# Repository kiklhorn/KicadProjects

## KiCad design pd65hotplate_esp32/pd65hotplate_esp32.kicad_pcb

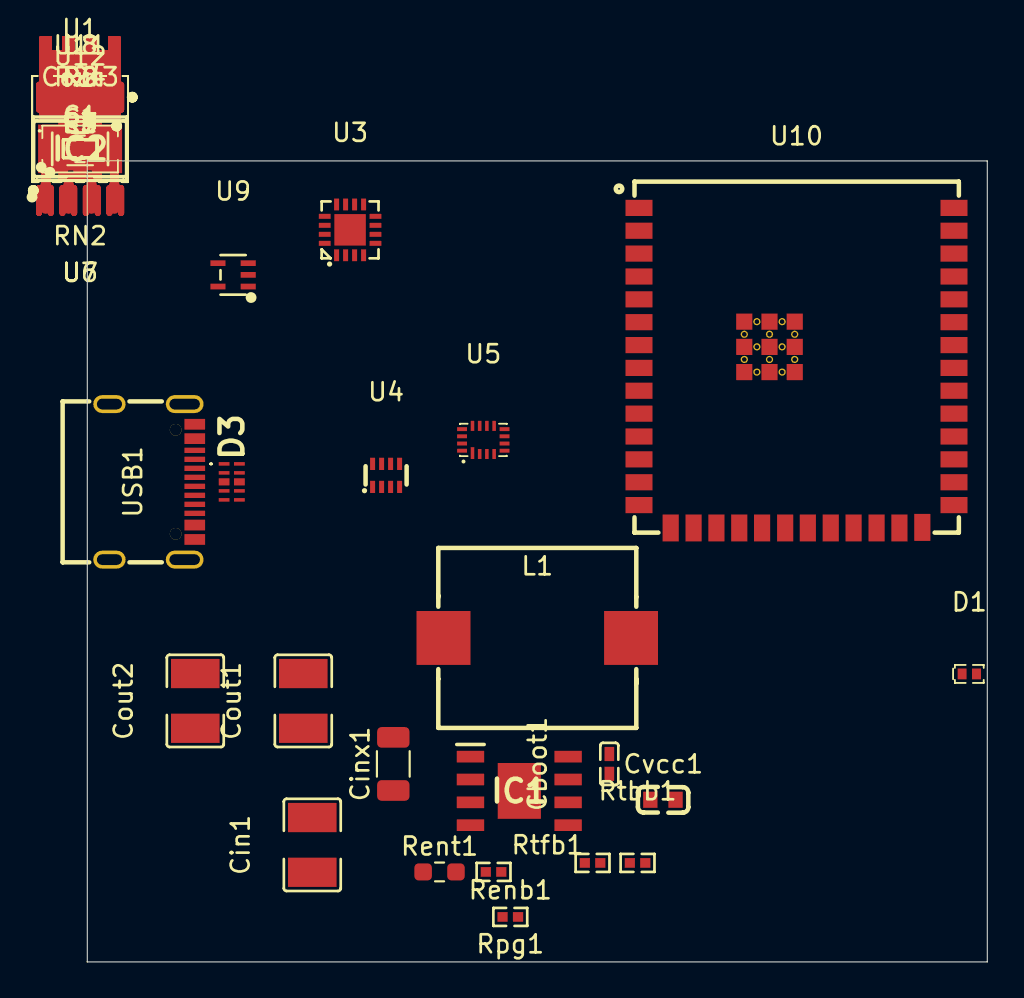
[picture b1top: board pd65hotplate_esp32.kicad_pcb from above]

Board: 2 copper layers, 50.0 x 44.5 mm, 42 parts (0 on the bottom side), 40 nets, no tracks yet.

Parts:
C1: 220n/100V; C_1206_3216Metric
C3: 105K50V; C_0603_1608Metric_Pad1.08x0.95mm_HandSolder
C4: 22p; C_0805_2012Metric_Pad1.18x1.45mm_HandSolder
Cboot1: GRM155R71A104KA01D; C0402
Cin1: GCM32DC72A475KE02L; C1210
Cinx1: 220n/100V; C_1206_3216Metric
Cout1, Cout2, Cout3: GRM32ER61C476KE15L; C1210
Cvcc1: EMK107B7105KA-T; C0603
D1: PESD24VS1UL-N; DFN1006-2L-RD
D3: PESD4USB5U-TTSX; PESD4USB5UTTSX
IC1: LMR36510FADDAR; SOIC127P600X170-9N
IC2: BQ25173QWDRCRQ1
L1: SDR1105-220ML; IND-SMD_L11.0-W10.0-2
R1: 920k; R_0603_1608Metric_Pad0.98x0.95mm_HandSolder
R2: 50k; R0402
R3: 10R; R_0603_1608Metric_Pad0.98x0.95mm_HandSolder
R4, R7, R8: 900k; R_0603_1608Metric_Pad0.98x0.95mm_HandSolder
R5: R_0603_1608Metric_Pad0.98x0.95mm_HandSolder
R6: R0402
R24: 10k; R0402
RN2: 100k; RES-ARRAY-SMD_16P-L3.8-W1.6-P0.50-BL
Renb1: CRCW0402100KFKED; R0402
Rent1: CRCW0402100KFKED; R_0603_1608Metric_Pad0.98x0.95mm_HandSolder
Rpg1: CRCW0402100KFKED; R0402
Rtbb1: CRCW040243K2FKED; R0402
Rtfb1: CRCW0402100KFKED; R0402
U1: RT9068GSP; ESOP-8_L4.9-W3.9-P1.27-LS6.0-BL-EP2.3
U3: HUSB238A; QFN-16_L3.0-W3.0-P0.50-BL-EP1.7
U4: LM66200DRLR; SOT-583-8_L2.1-W1.2-P0.50-LS1.6-BL
U5: FSA2567UMX; UMLP-16_L2.6-W1.8-P0.40-BL
U6, U7: 74HC4051PW,118; TSSOP-16_L5.0-W4.4-P0.65-LS6.4-BL
U8, U11: AGM60P90A; TDSON-8_L5.9-W5.2-P1.27-BL
U9: 74AHC1G14SE-7; SOT-353_L2.1-W1.3-P0.65-LS2.3-BR
U10: ESP32-S3-WROOM-1U-N16R8; WIRELM-SMD_ESP32-S3-WROOM-1U
U12: SY6280AAAC; TSOT-23-5_L2.9-W1.6-P0.95-LS2.8-BL
USB1: TYPEC-304A-ACP16G; USB-C-SMD_XUNPU_TYPEC-304A-ACP16W

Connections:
3V3: R7.1, R8.1, RN2.10 (R7.2), RN2.11 (R6.2), RN2.12 (R5.2), RN2.13 (R4.2), RN2.14 (R3.2), RN2.15 (R2.2), RN2.16 (R1.2), U3.5 (VDD), U4.2 (VOUT), U4.7 (VOUT), U5.14 (VCC), U6.16 (VCC), U7.16 (VCC), U9.5 (VCC), U10.11 (3V3)
3V3bck: U4.6 (VIN2), U12.1 (OUT)
3V3smps: C4.1, Cout2.2, Cout3.2, L1.1, Rpg1.2, Rtfb1.1, U4.3 (VIN1), U12.4 (EN), U12.5 (IN)
CC1: D3.1 (CH1), U3.3 (CC1), USB1.A5 (CC1)
CC2: D3.5 (CH4), U3.4 (CC2), USB1.B5 (CC2)
DN: D3.2 (CH2), U3.2 (D-), USB1.A7 (DN1), USB1.B7 (DN2)
DP: D3.4 (CH3), U3.1 (D+), USB1.A6 (DP1), USB1.B6 (DP2)
GND: C1.2, C3.2, Cin1.2, Cinx1.2, Cout1.1, Cout2.1, Cout3.1, Cvcc1.1, D3.3 (GND_1), D3.8 (GND_2), IC1.1 (PGND), IC1.9 (THERMAL), R2.2, R24.2, Renb1.2, Rtbb1.2, U1.5 (SHDN), U1.6 (GND), U1.7 (GND), U1.9 (EP), U3.17 (GND), U4.1 (GND), U4.4 (~ON), U4.5 (GND), U5.6 (GND), U6.4 (Y7), U6.6 (~E), U6.7 (VEE), U6.8 (GND), U7.4 (Y7), U7.7 (VEE), U7.8 (GND), U9.3 (GND), U10.12 (GND), U12.2 (GND), USB1.25 (EH), USB1.26 (EH), USB1.27 (EH), USB1.28 (EH), USB1.A1 (GND), USB1.A12 (GND), USB1.B1 (GND), USB1.B12 (GND)
unnamed: R5.2, R6.1
unnamed: Cboot1.2, IC1.7 (BOOT)
unnamed: IC1.3 (EN), Renb1.1, Rent1.2
unnamed: C4.2, IC1.5 (FB), Rtbb1.1, Rtfb1.2
unnamed: IC1.4 (PG), Rpg1.1
unnamed: Cboot1.1, IC1.8 (SW), L1.2
unnamed: Cvcc1.2, IC1.6 (VCC)
unnamed: RN2.1 (R1.1), U6.11 (S0)
unnamed: RN2.2 (R2.1), U6.10 (S1)
unnamed: RN2.3 (R3.1), U6.9 (S2)
unnamed: RN2.4 (R4.1), U7.11 (S0)
unnamed: RN2.5 (R5.1), U7.10 (S1)
unnamed: RN2.6 (R6.1), U7.9 (S2)
unnamed: RN2.7 (R7.1), U9.2 (A)
unnamed: R1.2, R2.1, U1.3 (FB)
unnamed: Cout1.2, R1.1, R3.1, U1.1 (VOUT), U1.2 (SENSE)
unnamed: R4.2, U3.8 (ADDR/ORIENT)
unnamed: R7.2, U3.6 (DBG_N)
unnamed: R8.2, U3.7 (EN_HVDCP/OUT1)
unnamed: R6.2, U3.15 (GATE)
unnamed: U3.10 (SCL/SNK_ISET), U5.12 (DAT)
unnamed: U3.9 (SDA/SNK_VSET), U5.4 (RST)
unnamed: R3.2, U3.16 (VBUS)
unnamed: U5.11 (2DAT), U7.3 (Z)
unnamed: U5.3 (2RST), U6.3 (Z)
unnamed: R4.1, U5.8 (CLK)
unnamed: U7.6 (~E), U9.4 (Y)
unnamed: R24.1, U12.3 (ISET)
SCL: U5.13 (1DAT), U10.10 (IO9)
SDA: U5.5 (1RST), U10.3 (IO8)
Vbus: C1.1, Cin1.1, Cinx1.1, IC1.2 (VIN), R5.1, Rent1.1, U1.8 (VIN), USB1.A4 (VBUS), USB1.A9 (VBUS), USB1.B4 (VBUS), USB1.B9 (VBUS)
i2c_gpio_SEL: U5.2 (Sel), U10.8 (IO7)

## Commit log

2024-03-18 prac
2024-04-01 add supercap backup
